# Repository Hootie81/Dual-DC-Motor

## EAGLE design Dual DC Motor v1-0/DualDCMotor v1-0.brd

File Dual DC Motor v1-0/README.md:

SPI_Motor
==========

This is a library for Hootie81's Dual DC Motor controller shield for the Spark Core

To use with Spark web IDE:

1. Create new APP (.ino automatically added by IDE)
2. Create a new set of tabs with the name "SPI_Motor" (which will create SPI_Motor.h and SPI_Motor.cpp)
3. Copy the code from the github files into the corresponding tabs (.h and .cpp)
4. Copy the code from github file Demo.ino into the .ino tab, writing over anything already in the tab
5. Verify the code
6. Enjoy!

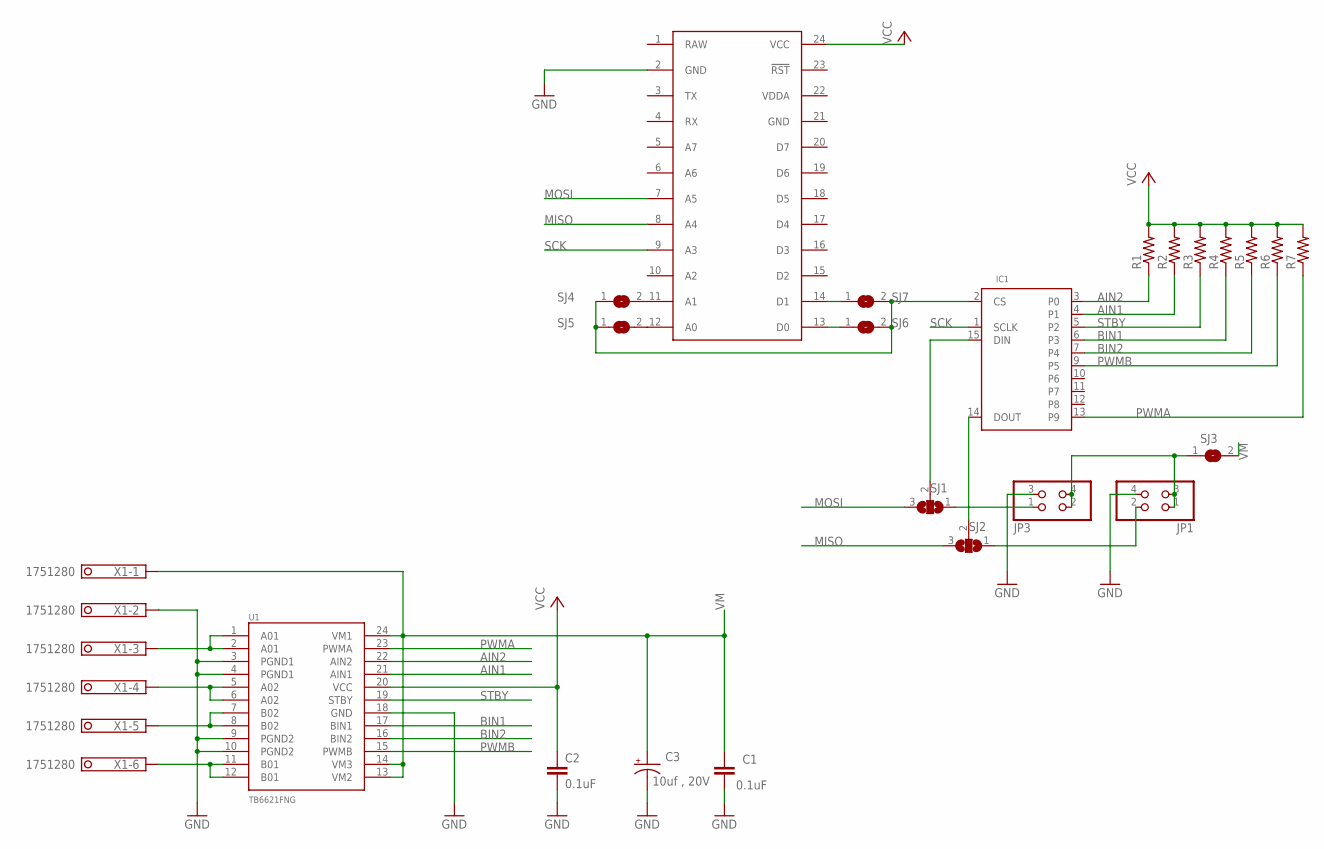
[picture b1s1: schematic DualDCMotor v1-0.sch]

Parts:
C1, C2: 0.1uF; 0402-CAP
C3: 10uf , 20V; EIA3528
IC1: MAX6966AEE; QSOP16
JP1, JP3: PINHD-2X02_2.54-SMD; 2X02SMD
R1, R2, R3, R4, R5, R6, R7: R-US_R0603; R0603
SJ1, SJ2: SJ2W; SJ_2
SJ3: SJW
SJ4, SJ5, SJ6, SJ7: SJ
U1: TB6621FNG; SSOP24
U$1: SPARK_CORECORE; SPARK_CORE
X1: 1751280

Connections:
A01: U1.1 (A01), U1.2 (A01), X1.3
A02: U1.5 (A02), U1.6 (A02), X1.4
AIN1: IC1.4 (P1), R2.1, U1.21 (AIN1)
AIN2: IC1.3 (P0), R1.1, U1.22 (AIN2)
B01: U1.11 (B01), U1.12 (B01), X1.6
B02: U1.7 (B02), U1.8 (B02), X1.5
BIN1: IC1.6 (P3), R4.1, U1.17 (BIN1)
BIN2: IC1.7 (P4), R5.1, U1.16 (BIN2)
GND: C1.2, C2.2, C3.C (-), IC1.8 (GND), JP1.4, JP3.3, U1.3 (PGND1), U1.4 (PGND1), U1.9 (PGND2), U1.10 (PGND2), U1.18 (GND), U$1.2 (GND), U$1.21 (GND), X1.2
MISO: SJ2.3, U$1.8 (A4)
MOSI: SJ1.3, U$1.7 (A5)
unnamed: JP3.1, SJ1.1
unnamed: JP1.2, SJ2.1
unnamed: IC1.15 (DIN), SJ1.2
unnamed: IC1.14 (DOUT), SJ2.2
unnamed: SJ4.2, U$1.11 (A1)
unnamed: SJ5.2, U$1.12 (A0)
unnamed: SJ6.1, U$1.13 (D0)
unnamed: SJ7.1, U$1.14 (D1)
unnamed: IC1.2 (CS), SJ4.1, SJ5.1, SJ6.2, SJ7.2
PWMA: IC1.13 (P9), R7.1, U1.23 (PWMA)
PWMB: IC1.9 (P5), R6.1, U1.15 (PWMB)
RAW: U$1.1 (RAW)
SCK: IC1.1 (SCLK), U$1.9 (A3)
STBY: IC1.5 (P2), R3.1, U1.19 (STBY)
VCC: C2.1, IC1.16 (VCC), R1.2, R2.2, R3.2, R4.2, R5.2, R6.2, R7.2, U1.20 (VCC), U$1.24 (VCC)
VDDA: U$1.22 (VDDA)
VM: C1.1, C3.A (+), SJ3.2, U1.13 (VM2), U1.14 (VM3), U1.24 (VM1), X1.1
VM2: JP1.1, JP1.3, JP3.2, JP3.4, SJ3.1

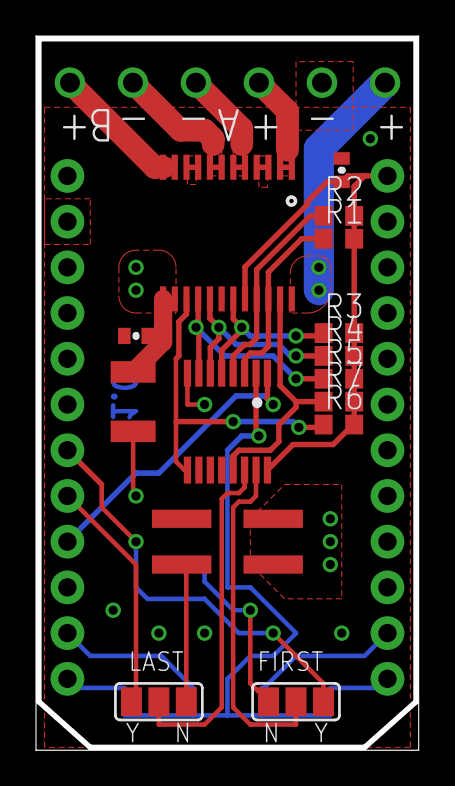
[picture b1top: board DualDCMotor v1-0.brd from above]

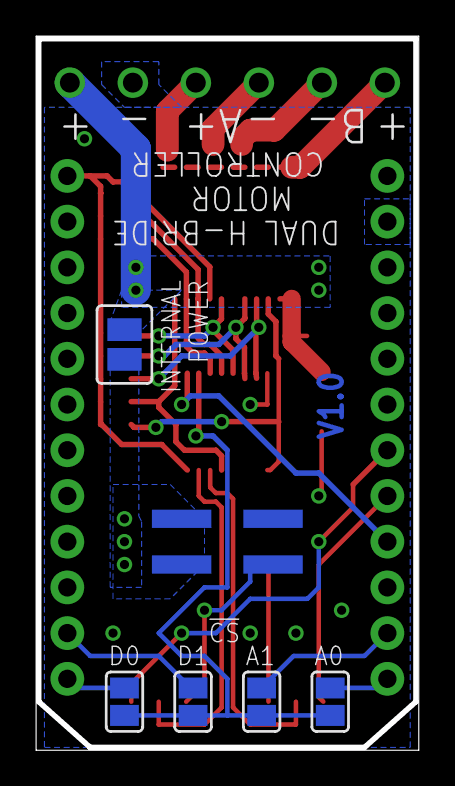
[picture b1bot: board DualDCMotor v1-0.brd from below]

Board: 2 copper layers, 21.3 x 39.7 mm, 23 parts (6 on the bottom side), 27 nets.

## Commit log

2014-07-26 Dual DC Motor shield for Spark Core
    A Shield for the spark core capable of driving 2 DC motors at 1.2A
    continuous and 3.2A peak. The board has a SPI interface with the Spark
    and allows a daisy-chain configuration where more of the same series of
    cards will not require any extra I/O , CS is selectable by
    solder-jumpers
2014-07-28 Pullup resistors added
    Added pullup resistors to datalines between i/o expander and h-bridge
    Fixed silkscreen layers
    Added gerbers
2014-08-01 Added Library
    Added a library to control the card, at this stage its untested and
    outputs the SPI data to the terminal window.
2014-08-01 Added License
2014-08-02 Added BOM
2014-09-12 Cleanup
    Removed old versions to avoid confusion
2014-10-09 Tested Library
    Working Library.
    Added stepper motor support.
2014-10-09 Working
    Removed double paste
2014-10-14 Added readme
    Added Readme.md and licence
